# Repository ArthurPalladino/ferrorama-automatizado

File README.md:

# Estação de Trem em Miniatura em Assembly AVR com ATmega328P

Este é o código fonte e o circuito de um projeto de automação desenvolvido como trabalho das minhas aulas de engenharia da computação, desenvolvido em AVR ASSEMBLY  para o microcontrolador ATMEGA328P.
Ele simula e controla uma estação de trem em miniatura, com dois trens, desvios de trilho e paradas automáticas nas estações.

---
  - Driver ponte H de motor para controlar dois trens individualmente.

  - A energia é transmitida pela placa para os trens em movimento por meio de um Slip Ring.

  - Quando um trem passa sobre um LDR, o servo motor correspondente gira, redirecionando automaticamente os trilhos.

  - Outros 2 sensores LDR adicionais detectam quando um trem chega à estação, parando o trem correspondente até que o outro se aproxime.

  - 4 servo motores controlados via PWM gerado por software.

  - Velocidade totalmente controlável e reversão completa por meio de um potenciômetro.
    
---

🎥 Vídeo do projeto: https://youtu.be/FEgj6yQy-WY

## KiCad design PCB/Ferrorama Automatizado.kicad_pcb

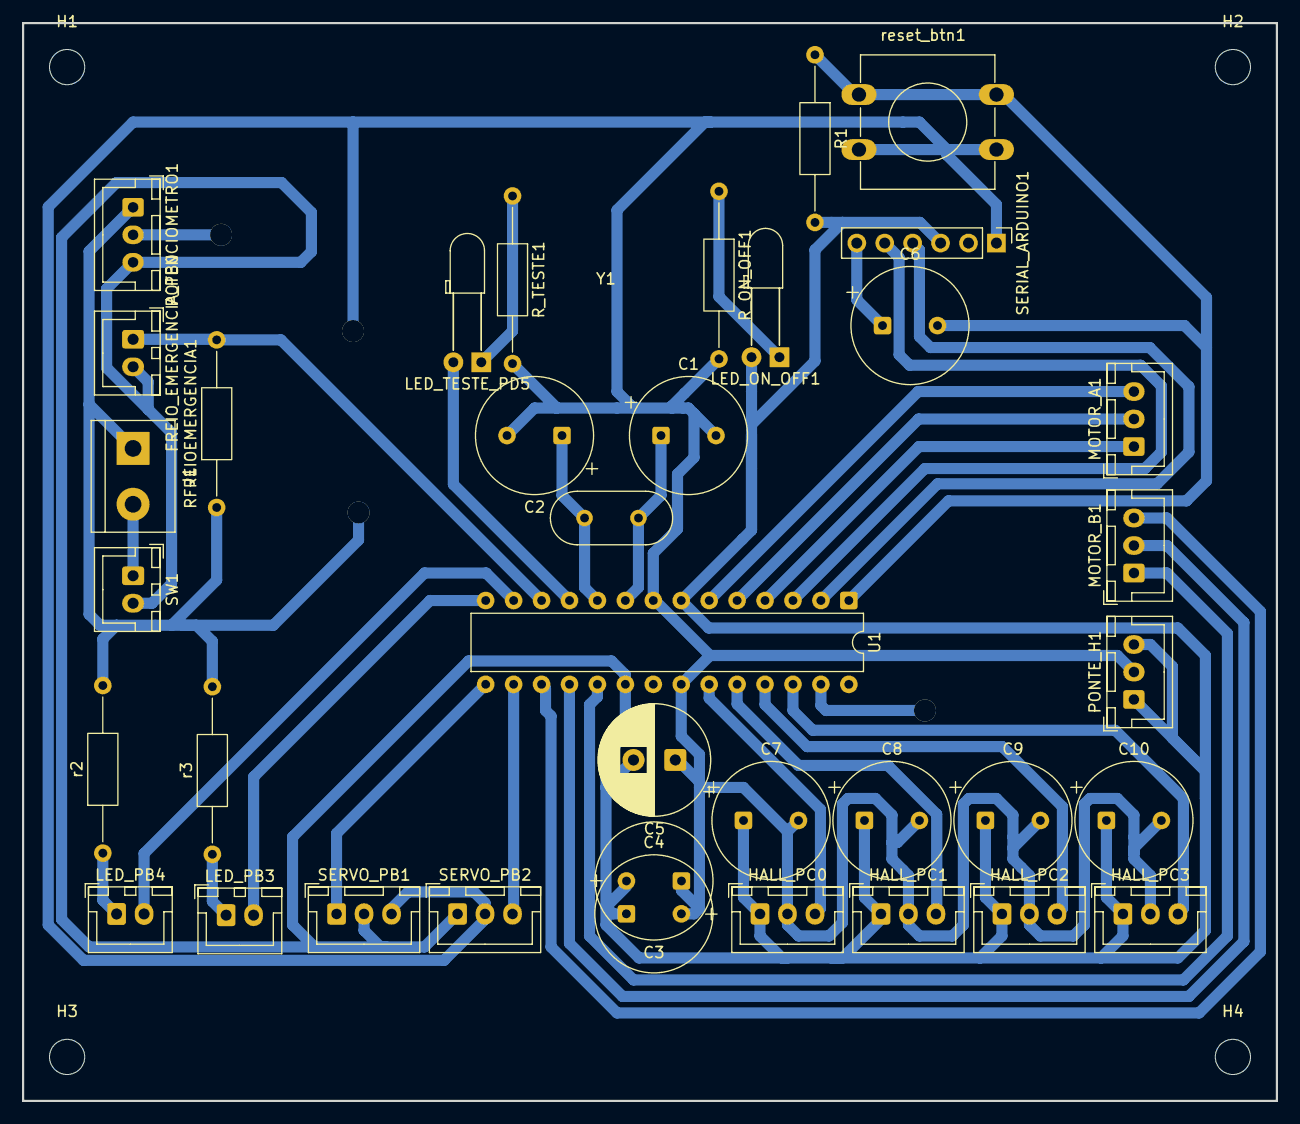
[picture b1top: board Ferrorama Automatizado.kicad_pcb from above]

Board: 2 copper layers, 114.0 x 98.0 mm, 41 parts (0 on the bottom side), 30 nets.

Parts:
C1, C2: 22pF; CP_Radial_Tantal_D10.5mm_P5.00mm
C3, C4, C6, C7, C8, C9, C10: 100nF; CP_Radial_Tantal_D10.5mm_P5.00mm
C5: 10uF; CP_Radial_D10.0mm_P3.80mm
FREIO_EMERGENCIA_PB0: FREIO EMERGENCIA; JST_XH_B2B-XH-A_1x02_P2.50mm_Vertical
H1, H2, H3, H4: MountingHole; MountingHole_3.2mm_M3
HALL_PC0, HALL_PC1, HALL_PC2, HALL_PC3: Screw_Terminal_01x03; JST_XH_B3B-XH-A_1x03_P2.50mm_Vertical
J1: ENTRADA ENERGIA 5V; TerminalBlock_bornier-2_P5.08mm
LED_ON_OFF1: LED ARDUINO ON OFF; LED_D3.0mm_Horizontal_O6.35mm_Z2.0mm
LED_PB3, LED_PB4: LED; JST_XH_B2B-XH-A_1x02_P2.50mm_Vertical
LED_TESTE_PD5: LED; LED_D3.0mm_Horizontal_O6.35mm_Z2.0mm
MOTOR_A1: Screw_Terminal_01x03; JST_XH_B3B-XH-A_1x03_P2.50mm_Vertical
MOTOR_B1: Screw_Terminal_01x03; JST_XH_B3B-XH-A_1x03_P2.50mm_Vertical
PONTE_H1: Screw_Terminal_01x03; JST_XH_B3B-XH-A_1x03_P2.50mm_Vertical
POTENCIOMETRO1: Screw_Terminal_01x03; JST_XH_B3B-XH-A_1x03_P2.50mm_Vertical
R1: 10K; R_Axial_DIN0207_L6.3mm_D2.5mm_P15.24mm_Horizontal
RFREIOEMERGENCIA1: 10K; R_Axial_DIN0207_L6.3mm_D2.5mm_P15.24mm_Horizontal
R_ON_OFF1: RESISTOR LED ON OFF; R_Axial_DIN0207_L6.3mm_D2.5mm_P15.24mm_Horizontal
R_TESTE1: RESISTOR LED TESTE; R_Axial_DIN0207_L6.3mm_D2.5mm_P15.24mm_Horizontal
SERIAL_ARDUINO1: Screw_Terminal_01x06; PinHeader_1x06_P2.54mm_Vertical
SERVO_PB1, SERVO_PB2: Motor_Servo; JST_XH_B3B-XH-A_1x03_P2.50mm_Vertical
SW1: CHAVE ON/OFF; JST_XH_B2B-XH-A_1x02_P2.50mm_Vertical
U1: ATmega328P-P; DIP-28_W7.62mm
Y1: Crystal; Crystal_HC18-U_Vertical
r2, r3: RESISTOR LED ON OFF; R_Axial_DIN0207_L6.3mm_D2.5mm_P15.24mm_Horizontal
reset_btn1: FREIO EMERGENCIA; SW_PUSH-12mm

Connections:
FREIO EMERGENCIA: FREIO_EMERGENCIA_PB0.1, RFREIOEMERGENCIA1.2, U1.12 (PD6)
GND: C1.2, C2.2, C3.1, C4.2, C5.1, C7.2, C8.2, C9.2, C10.2, HALL_PC0.2, HALL_PC1.2, HALL_PC2.2, HALL_PC3.2, J1.1, PONTE_H1.2, POTENCIOMETRO1.1, RFREIOEMERGENCIA1.1, R_ON_OFF1.2, R_TESTE1.2, SERIAL_ARDUINO1.1, SERVO_PB1.3 (-), SERVO_PB2.2 (+), U1.8 (GND), U1.22 (GND), r2.2, r3.2, reset_btn1.2
HALL1: HALL_PC0.3, U1.23 (PC0)
HALL2: HALL_PC1.3, U1.24 (PC1)
HALL3: HALL_PC2.3, U1.25 (PC2)
HALL4: HALL_PC3.3, U1.26 (PC3)
LED TESTE: LED_TESTE_PD5.2 (A), U1.11 (PD5)
LED_VERDE_1: LED_PB3.2 (A), U1.14 (PB0)
LED_VERDE_2: LED_PB4.2 (A), U1.13 (PD7)
MOTOR A1: MOTOR_A1.1, U1.4 (PD2)
MOTOR A2: MOTOR_A1.3, U1.6 (PD4)
MOTOR B1: MOTOR_B1.2, U1.18 (PB4)
MOTOR B2: MOTOR_B1.1, U1.19 (PB5)
unnamed: LED_ON_OFF1.1 (K), R_ON_OFF1.1
unnamed: LED_PB3.1 (K), r3.1
unnamed: LED_PB4.1 (K), r2.1
unnamed: LED_TESTE_PD5.1 (K), R_TESTE1.1
unnamed: C6.1, SERIAL_ARDUINO1.6
unnamed: C1.1, U1.9 (XTAL1/PB6), Y1.2
unnamed: C2.1, U1.10 (XTAL2/PB7), Y1.1
PINO_RESET: C6.2, R1.1, U1.1 (~RESET/PC6), reset_btn1.1
POTENCIOMETRO: POTENCIOMETRO1.2, U1.27 (PC4)
PWM_MOTOR_1: MOTOR_A1.2, U1.5 (PD3)
PWM_MOTOR_2: MOTOR_B1.3, U1.17 (PB3)
RXD: SERIAL_ARDUINO1.5, U1.3 (PD1)
SERVO1: SERVO_PB1.1 (PWM), U1.15 (PB1)
SERVO2: SERVO_PB2.3 (-), U1.16 (PB2)
SVCC: C3.2, C4.1, C5.2, C7.1, C8.1, C9.1, C10.1, FREIO_EMERGENCIA_PB0.2, HALL_PC0.1, HALL_PC1.1, HALL_PC2.1, HALL_PC3.1, LED_ON_OFF1.2 (A), PONTE_H1.1, PONTE_H1.3, POTENCIOMETRO1.3, R1.2, SERIAL_ARDUINO1.3, SERVO_PB1.2 (+), SERVO_PB2.1 (PWM), SW1.2, U1.7 (VCC), U1.20 (AVCC)
TXD: SERIAL_ARDUINO1.4, U1.2 (PD0)
VCC: J1.2, SW1.1

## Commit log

2025-11-18 Add: circuito eletrônico da pcb
2025-11-18 Add project description
2025-12-19 Add: avr assembler code
